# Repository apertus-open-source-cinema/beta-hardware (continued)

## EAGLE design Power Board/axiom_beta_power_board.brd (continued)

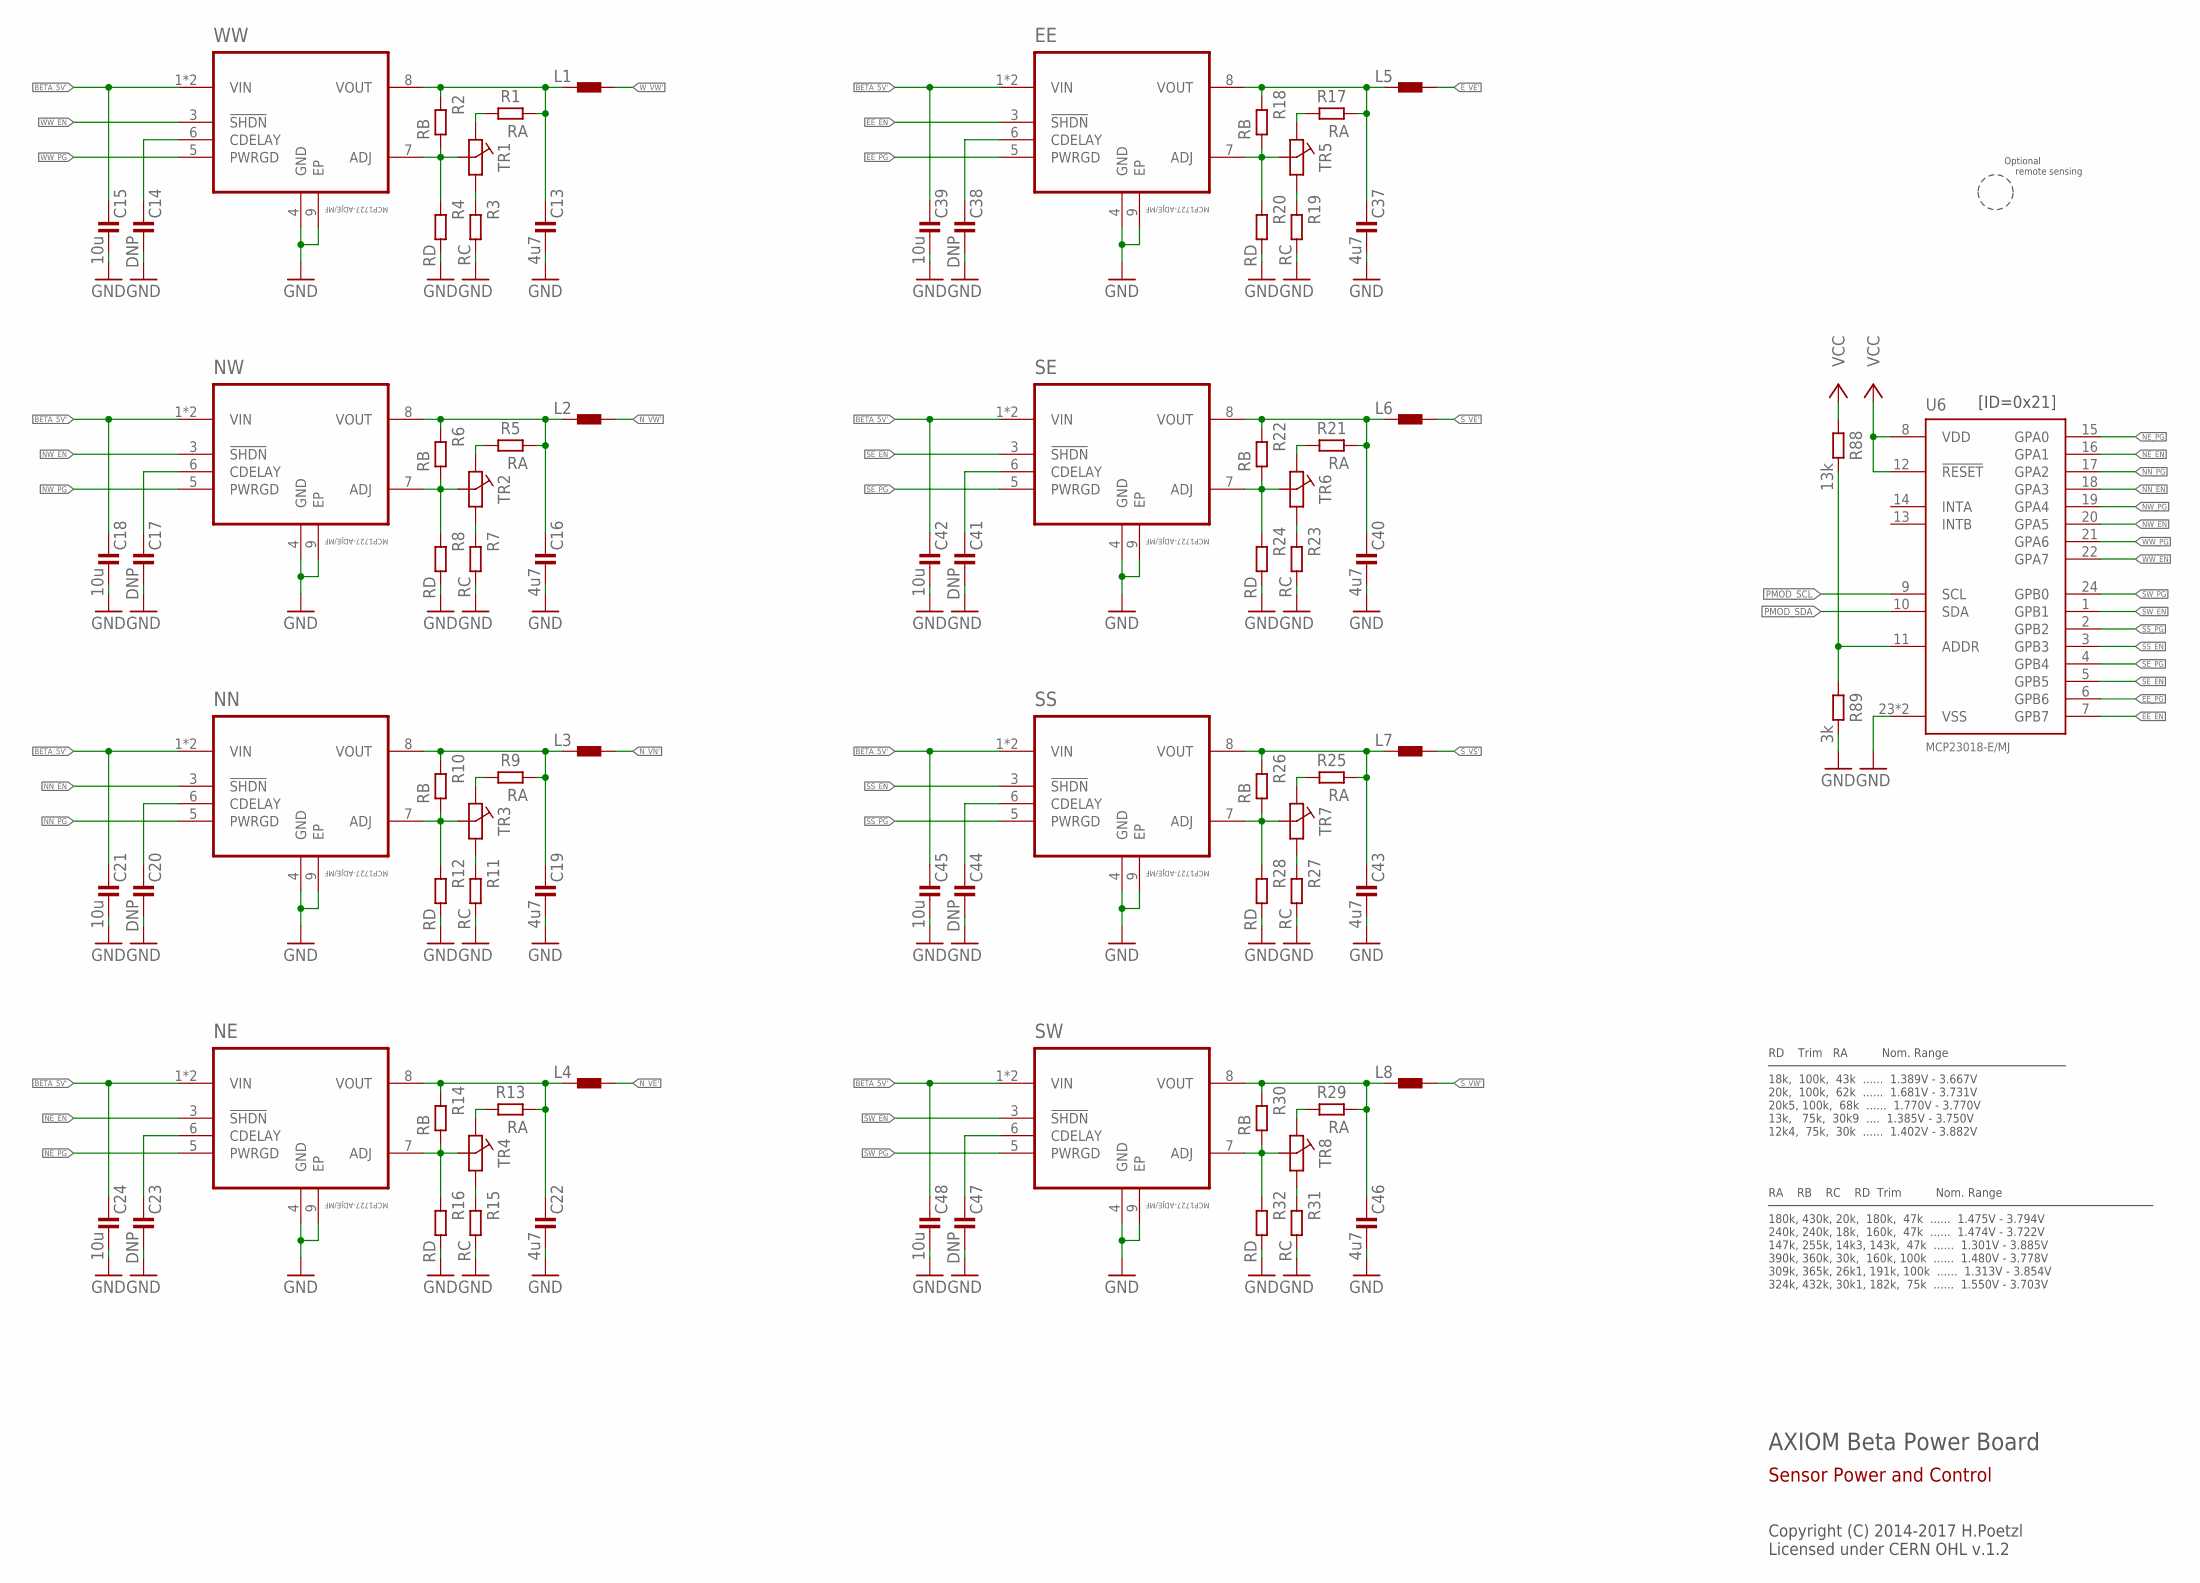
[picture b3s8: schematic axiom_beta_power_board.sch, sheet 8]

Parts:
C13, C16, C19, C22, C37, C40, C43, C46: 4u7; 0603-B
C14, C17, C20, C23, C38, C41, C44, C47: DNP; 0402-B
C15, C18, C21, C24, C39, C42, C45, C48: 10u; 0603-B
EE: MCP1727-ADJE/MF; DFN65P300X300X100-9N
L1, L2, L3, L4, L5, L6, L7, L8: L0805-B; 0805-B
NE: MCP1727-ADJE/MF; DFN65P300X300X100-9N
NN: MCP1727-ADJE/MF; DFN65P300X300X100-9N
NW: MCP1727-ADJE/MF; DFN65P300X300X100-9N
R1, R5, R9, R13, R17, R21, R25, R29: RA; 0402-B
R2, R6, R10, R14, R18, R22, R26, R30: RB; 0402-B
R3, R7, R11, R15, R19, R23, R27, R31: RC; 0402-B
R4, R8, R12, R16, R20, R24, R28, R32: RD; 0402-B
R88: 13k; 0402-B
R89: 3k; 0402-B
SE: MCP1727-ADJE/MF; DFN65P300X300X100-9N
SS: MCP1727-ADJE/MF; DFN65P300X300X100-9N
SW: MCP1727-ADJE/MF; DFN65P300X300X100-9N
TR1, TR2, TR3, TR4, TR5, TR6, TR7, TR8: PVZ2A; TRIM-PVZ2A
U6: MCP23018-E/MJ; QFN50P400X400X80-25N
WW: MCP1727-ADJE/MF; DFN65P300X300X100-9N

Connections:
BETA_5V': C15.1, C18.1, C21.1, C24.1, C39.1, C42.1, C45.1, C48.1, EE.1 (VIN), EE.2 (VIN), NE.1 (VIN), NE.2 (VIN), NN.1 (VIN), NN.2 (VIN), NW.1 (VIN), NW.2 (VIN), SE.1 (VIN), SE.2 (VIN), SS.1 (VIN), SS.2 (VIN), SW.1 (VIN), SW.2 (VIN), WW.1 (VIN), WW.2 (VIN); also elsewhere on the board
EE_EN: EE.3 (!SHDN), U6.7 (GPB7)
EE_PG: EE.5 (PWRGD), U6.6 (GPB6)
E_VE': L5.2; also elsewhere on the board
GND: C13.2, C14.2, C15.2, C16.2, C17.2, C18.2, C19.2, C20.2, C21.2, C22.2, C23.2, C24.2, C37.2, C38.2, C39.2, C40.2, C41.2, C42.2, C43.2, C44.2, C45.2, C46.2, C47.2, C48.2, EE.4 (GND), EE.9 (EP), NE.4 (GND), NE.9 (EP), NN.4 (GND), NN.9 (EP), NW.4 (GND), NW.9 (EP), R3.2, R4.2, R7.2, R8.2, R11.2, R12.2, R15.2, R16.2, R19.2, R20.2, R23.2, R24.2, R27.2, R28.2, R31.2, R32.2, R89.2, SE.4 (GND), SE.9 (EP), SS.4 (GND), SS.9 (EP), SW.4 (GND), SW.9 (EP), U6.23 (VSS), U6.25 (VSS), WW.4 (GND), WW.9 (EP); also elsewhere on the board
unnamed: C13.1, L1.1, R1.2, R2.1, WW.8 (VOUT)
unnamed: R2.2, R4.1, TR1.2 (B), WW.7 (ADJ)
unnamed: R3.1, TR1.1 (A)
unnamed: C14.1, WW.6 (CDELAY)
unnamed: R1.1, TR1.3 (C)
unnamed: C16.1, L2.1, NW.8 (VOUT), R5.2, R6.1
unnamed: NW.7 (ADJ), R6.2, R8.1, TR2.2 (B)
unnamed: R7.1, TR2.1 (A)
unnamed: C17.1, NW.6 (CDELAY)
unnamed: C19.1, L3.1, NN.8 (VOUT), R9.2, R10.1
unnamed: NN.7 (ADJ), R10.2, R12.1, TR3.2 (B)
unnamed: R5.1, TR2.3 (C)
unnamed: C20.1, NN.6 (CDELAY)
unnamed: C22.1, L4.1, NE.8 (VOUT), R13.2, R14.1
unnamed: NE.7 (ADJ), R14.2, R16.1, TR4.2 (B)
unnamed: R11.1, TR3.1 (A)
unnamed: C23.1, NE.6 (CDELAY)
unnamed: C37.1, EE.8 (VOUT), L5.1, R17.2, R18.1
unnamed: EE.7 (ADJ), R18.2, R20.1, TR5.2 (B)
unnamed: R9.1, TR3.3 (C)
unnamed: C38.1, EE.6 (CDELAY)
unnamed: R15.1, TR4.1 (A)
unnamed: C40.1, L6.1, R21.2, R22.1, SE.8 (VOUT)
unnamed: R22.2, R24.1, SE.7 (ADJ), TR6.2 (B)
unnamed: R13.1, TR4.3 (C)
unnamed: C41.1, SE.6 (CDELAY)
unnamed: R19.1, TR5.1 (A)
unnamed: C43.1, L7.1, R25.2, R26.1, SS.8 (VOUT)
unnamed: R26.2, R28.1, SS.7 (ADJ), TR7.2 (B)
unnamed: R17.1, TR5.3 (C)
unnamed: C44.1, SS.6 (CDELAY)
unnamed: R23.1, TR6.1 (A)
unnamed: C46.1, L8.1, R29.2, R30.1, SW.8 (VOUT)
unnamed: R30.2, R32.1, SW.7 (ADJ), TR8.2 (B)
unnamed: R21.1, TR6.3 (C)
unnamed: C47.1, SW.6 (CDELAY)
unnamed: R27.1, TR7.1 (A)
unnamed: R25.1, TR7.3 (C)
unnamed: R31.1, TR8.1 (A)
unnamed: R29.1, TR8.3 (C)
unnamed: R88.2, R89.1, U6.11 (ADDR)
NE_EN: NE.3 (!SHDN), U6.16 (GPA1)
NE_PG: NE.5 (PWRGD), U6.15 (GPA0)
NN_EN: NN.3 (!SHDN), U6.18 (GPA3)
NN_PG: NN.5 (PWRGD), U6.17 (GPA2)
NW_EN: NW.3 (!SHDN), U6.20 (GPA5)
NW_PG: NW.5 (PWRGD), U6.19 (GPA4)
N_VE': L4.2; also elsewhere on the board
N_VN': L3.2; also elsewhere on the board
N_VW': L2.2; also elsewhere on the board
PMOD_SCL: U6.9 (SCL); also elsewhere on the board
PMOD_SDA: U6.10 (SDA); also elsewhere on the board
SE_EN: SE.3 (!SHDN), U6.5 (GPB5)
SE_PG: SE.5 (PWRGD), U6.4 (GPB4)
SS_EN: SS.3 (!SHDN), U6.3 (GPB3)
SS_PG: SS.5 (PWRGD), U6.2 (GPB2)
SW_EN: SW.3 (!SHDN), U6.1 (GPB1)
SW_PG: SW.5 (PWRGD), U6.24 (GPB0)
S_VE': L6.2; also elsewhere on the board
S_VS': L7.2; also elsewhere on the board
S_VW': L8.2; also elsewhere on the board
VCC: R88.1, U6.8 (VDD), U6.12 (!RESET); also elsewhere on the board
WW_EN: U6.22 (GPA7), WW.3 (!SHDN)
WW_PG: U6.21 (GPA6), WW.5 (PWRGD)
W_VW': L1.2; also elsewhere on the board

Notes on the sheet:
AXIOM Beta Power Board
Copyright (C) 2014-2017 H.Poetzl Licensed under CERN OHL v.1.2
Sensor Power and Control
[ID=0x21]
RD Trim RA Nom. Range 18k, 100k, 43k ...... 1.389V - 3.667V 20k, 100k, 62k ...... 1.681V - 3.731V 20k5, 100k, 68k ...... 1.770V - 3.770V 13k, 75k, 30k9 .... 1.385V - 3.750V 12k4, 75k, 30k ...... 1.402V - 3.882V
Optional remote sensing
RA RB RC RD Trim Nom. Range 180k, 430k, 20k, 180k, 47k ...... 1.475V - 3.794V 240k, 240k, 18k, 160k, 47k ...... 1.474V - 3.722V 147k, 255k, 14k3, 143k, 47k ...... 1.301V - 3.885V 390k, 360k, 30k, 160k, 100k ...... 1.480V - 3.778V 309k, 365k, 26k1, 191k, 100k ...... 1.313V - 3.854V 324k, 432k, 30k1,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

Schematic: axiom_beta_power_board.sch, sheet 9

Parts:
R51, R52, R53, R54, R55, R56, R57, R58, R59, R60, R61, R62: R1206-B; 1206-B
R73: 750R; 0402-B
R74: 1k27; 0402-B
R75: 430R; 0402-B
R76: 0R; 0402-B
R77: 100R; 0402-B
R78: 560R; 0402-B
U17, U18, U19, U20, U23, U24: PAC1720; DFN3X3_10LEAD

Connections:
E_VE: R57.2, U19.2 (SENSE1-); also elsewhere on the board
E_VE': R57.1, U19.1 (SENSE1+); also elsewhere on the board
GND: R73.2, R74.2, R75.2, R76.2, R77.2, R78.2, U17.5 (GND), U17.EPAD (GND), U18.5 (GND), U18.EPAD (GND), U19.5 (GND), U19.EPAD (GND), U20.5 (GND), U20.EPAD (GND), U23.5 (GND), U23.EPAD (GND), U24.5 (GND), U24.EPAD (GND); also elsewhere on the board
unnamed: R73.1, U18.6 (ASEL)
unnamed: R75.1, U24.6 (ASEL)
unnamed: R78.1, U23.6 (ASEL)
unnamed: R74.1, U20.6 (ASEL)
unnamed: R76.1, U19.6 (ASEL)
unnamed: R77.1, U17.6 (ASEL)
N_VE: R54.2, U20.4 (SENSE2-); also elsewhere on the board
N_VE': R54.1, U20.3 (SENSE2+); also elsewhere on the board
N_VN: R53.2, U20.2 (SENSE1-); also elsewhere on the board
N_VN': R53.1, U20.1 (SENSE1+); also elsewhere on the board
N_VW: R52.2, U18.4 (SENSE2-); also elsewhere on the board
N_VW': R52.1, U18.3 (SENSE2+); also elsewhere on the board
PCIE_VCCIO: R61.2, U23.2 (SENSE1-)
PMOD_SCL: U17.9 (SMCLK), U18.9 (SMCLK), U19.9 (SMCLK), U20.9 (SMCLK), U23.9 (SMCLK), U24.9 (SMCLK); also elsewhere on the board
PMOD_SDA: U17.8 (SMDATA), U18.8 (SMDATA), U19.8 (SMDATA), U20.8 (SMDATA), U23.8 (SMDATA), U24.8 (SMDATA); also elsewhere on the board
S_VE: R58.2, U19.4 (SENSE2-); also elsewhere on the board
S_VE': R58.1, U19.3 (SENSE2+); also elsewhere on the board
S_VS: R59.2, U17.2 (SENSE1-); also elsewhere on the board
S_VS': R59.1, U17.1 (SENSE1+); also elsewhere on the board
S_VW: R60.2, U17.4 (SENSE2-); also elsewhere on the board
S_VW': R60.1, U17.3 (SENSE2+); also elsewhere on the board
VCC: U17.10 (VDD), U18.10 (VDD), U19.10 (VDD), U20.10 (VDD), U23.10 (VDD), U24.10 (VDD); also elsewhere on the board
VCCIO: R55.1, R56.1, R61.1, R62.1, U23.1 (SENSE1+), U23.3 (SENSE2+), U24.1 (SENSE1+), U24.3 (SENSE2+); also elsewhere on the board
VCCO_13: R56.2, U24.4 (SENSE2-); also elsewhere on the board
VCCO_34: R62.2, U23.4 (SENSE2-); also elsewhere on the board
VCCO_35: R55.2, U24.2 (SENSE1-); also elsewhere on the board
W_VW: R51.2, U18.2 (SENSE1-); also elsewhere on the board
W_VW': R51.1, U18.1 (SENSE1+); also elsewhere on the board

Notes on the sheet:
AXIOM Beta Power Board
Copyright (C) 2014-2017 H.Poetzl Licensed under CERN OHL v.1.2
Sensor Power Sensing
[0x48]
[0x49]
[0x4B]
[0x4D]
[0x4A]
[0x4C]

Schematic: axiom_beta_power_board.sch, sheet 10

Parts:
C49, C52, C55, C58, C61: 4u7; 0603-B
C50, C53, C56, C59, C62: DNP; 0402-B
C51, C54, C57, C60, C63: 10u; 0603-B
L9, L10, L11, L12, L13: L0805-A; 0805-A
MCN: MCP1727-ADJE/MF; DFN65P300X300X100-9N
MCS: MCP1727-ADJE/MF; DFN65P300X300X100-9N
MXN: MCP1727-ADJE/MF; DFN65P300X300X100-9N
MXS: MCP1727-ADJE/MF; DFN65P300X300X100-9N
R33, R35, R39, R41: RD; 0402-B
R34, R36, R40, R42: RC; 0402-B
R37: 102k; 0402-B
R38: 20k; 0402-B
R67, R68, R69, R70, R71, R72: R1206-B; 1206-B
R81: 2k0; 0402-B
R82: 1k6; 0402-B
R83: 2k7; 0402-B
R90: 15k; 0402-B
R91: 1k; 0402-B
U7: MCP23018-E/MJ; QFN50P400X400X80-25N
U14, U15, U22: PAC1720; DFN3X3_10LEAD
VIO: MCP1727-ADJE/MF; DFN65P300X300X100-9N

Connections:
BETA_5V: R70.1, U22.3 (SENSE2+); also elsewhere on the board
BETA_5V': C51.1, C54.1, C57.1, C60.1, C63.1, MCN.1 (VIN), MCN.2 (VIN), MCS.1 (VIN), MCS.2 (VIN), MXN.1 (VIN), MXN.2 (VIN), MXS.1 (VIN), MXS.2 (VIN), R70.2, U22.4 (SENSE2-), VIO.1 (VIN), VIO.2 (VIN); also elsewhere on the board
CSO_NE_V: R67.2, U14.2 (SENSE1-); also elsewhere on the board
CSO_N_V': L12.2, R67.1, U14.1 (SENSE1+)
CSO_SW_V: R71.2, U15.2 (SENSE1-); also elsewhere on the board
CSO_S_V': L10.2, R71.1, U15.1 (SENSE1+)
GND: C49.2, C50.2, C51.2, C52.2, C53.2, C54.2, C55.2, C56.2, C57.2, C58.2, C59.2, C60.2, C61.2, C62.2, C63.2, MCN.4 (GND), MCN.9 (EP), MCS.4 (GND), MCS.9 (EP), MXN.4 (GND), MXN.9 (EP), MXS.4 (GND), MXS.9 (EP), R34.2, R36.2, R38.2, R40.2, R42.2, R81.2, R82.2, R83.2, R91.2, U7.23 (VSS), U7.25 (VSS), U14.5 (GND), U14.EPAD (GND), U15.5 (GND), U15.EPAD (GND), U22.5 (GND), U22.EPAD (GND), VIO.4 (GND), VIO.9 (EP); also elsewhere on the board
MCN_EN: MCN.3 (!SHDN), U7.18 (GPA3)
MCN_PG: MCN.5 (PWRGD), U7.17 (GPA2)
MCS_EN: MCS.3 (!SHDN), U7.22 (GPA7)
MCS_PG: MCS.5 (PWRGD), U7.21 (GPA6)
MXN_EN: MXN.3 (!SHDN), U7.16 (GPA1)
MXN_PG: MXN.5 (PWRGD), U7.15 (GPA0)
MXS_EN: MXS.3 (!SHDN), U7.1 (GPB1)
MXS_PG: MXS.5 (PWRGD), U7.24 (GPB0)
unnamed: C49.1, L9.1, MXS.8 (VOUT), R41.1
unnamed: MXS.7 (ADJ), R41.2, R42.1
unnamed: C50.1, MXS.6 (CDELAY)
unnamed: R81.1, U14.6 (ASEL)
unnamed: R83.1, U15.6 (ASEL)
unnamed: C52.1, L10.1, MCS.8 (VOUT), R39.1
unnamed: MCS.7 (ADJ), R39.2, R40.1
unnamed: C53.1, MCS.6 (CDELAY)
unnamed: R82.1, U22.6 (ASEL)
unnamed: C55.1, L11.1, R37.1, VIO.8 (VOUT)
unnamed: R37.2, R38.1, VIO.7 (ADJ)
unnamed: C56.1, VIO.6 (CDELAY)
unnamed: C58.1, L12.1, MCN.8 (VOUT), R35.1
unnamed: MCN.7 (ADJ), R35.2, R36.1
unnamed: C59.1, MCN.6 (CDELAY)
unnamed: C61.1, L13.1, MXN.8 (VOUT), R33.1
unnamed: MXN.7 (ADJ), R33.2, R34.1
unnamed: C62.1, MXN.6 (CDELAY)
unnamed: R90.2, R91.1, U7.11 (ADDR)
PCIE_N_V: R68.2, U14.4 (SENSE2-); also elsewhere on the board
PCIE_N_V': L13.2, R68.1, U14.3 (SENSE2+)
PCIE_S_V: R72.2, U15.4 (SENSE2-); also elsewhere on the board
PCIE_S_V': L9.2, R72.1, U15.3 (SENSE2+)
PMOD_SCL: U7.9 (SCL), U14.9 (SMCLK), U15.9 (SMCLK), U22.9 (SMCLK); also elsewhere on the board
PMOD_SDA: U7.10 (SDA), U14.8 (SMDATA), U15.8 (SMDATA), U22.8 (SMDATA); also elsewhere on the board
VCC: R90.1, U7.8 (VDD), U7.12 (!RESET), U14.10 (VDD), U15.10 (VDD), U22.10 (VDD); also elsewhere on the board
VCCIO: L11.2; also elsewhere on the board
VIO_EN: U7.20 (GPA5), VIO.3 (!SHDN)
VIO_PG: U7.19 (GPA4), VIO.5 (PWRGD)
ZED_5V: R69.1, U22.1 (SENSE1+); also elsewhere on the board
ZED_5V': R69.2, U22.2 (SENSE1-); also elsewhere on the board

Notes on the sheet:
AXIOM Beta Power Board
Copyright (C) 2014-2017 H.Poetzl Licensed under CERN OHL v.1.2
Power, Control and Sensing
[ID=0x20]
[0x29]
[0x28]
[0x2A]

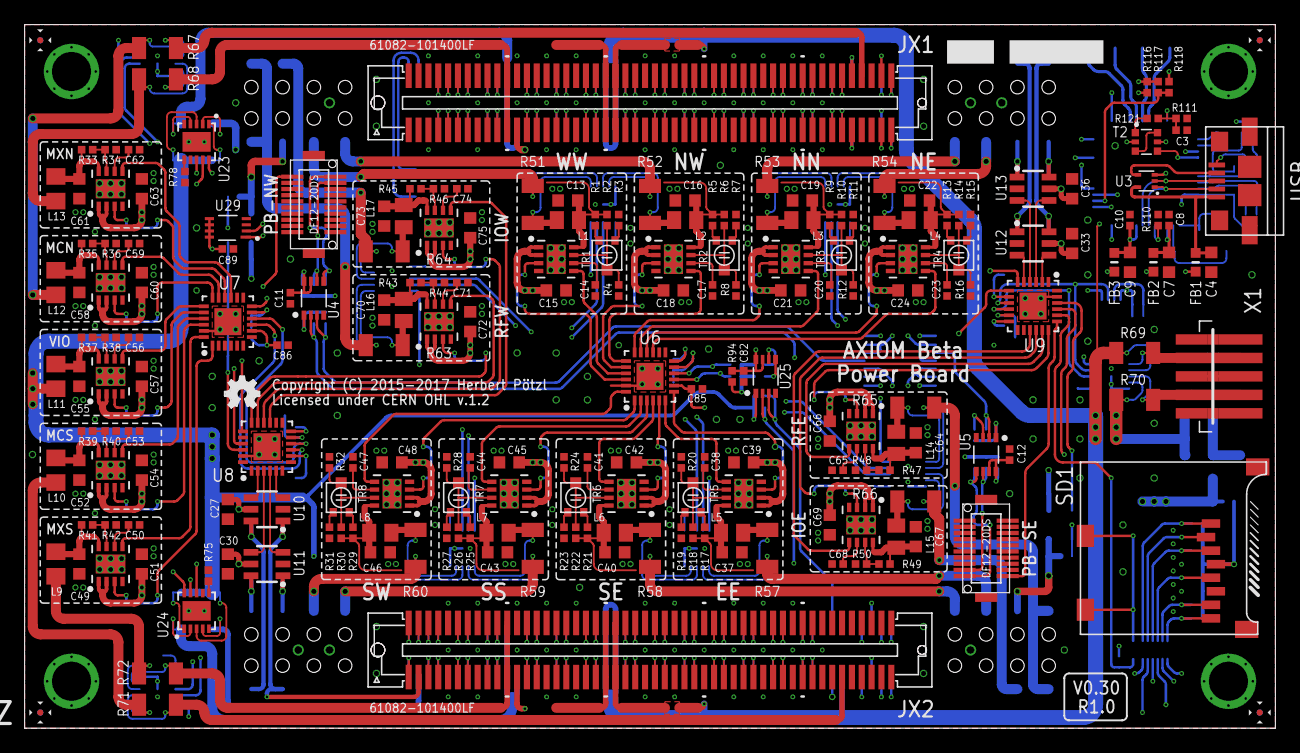
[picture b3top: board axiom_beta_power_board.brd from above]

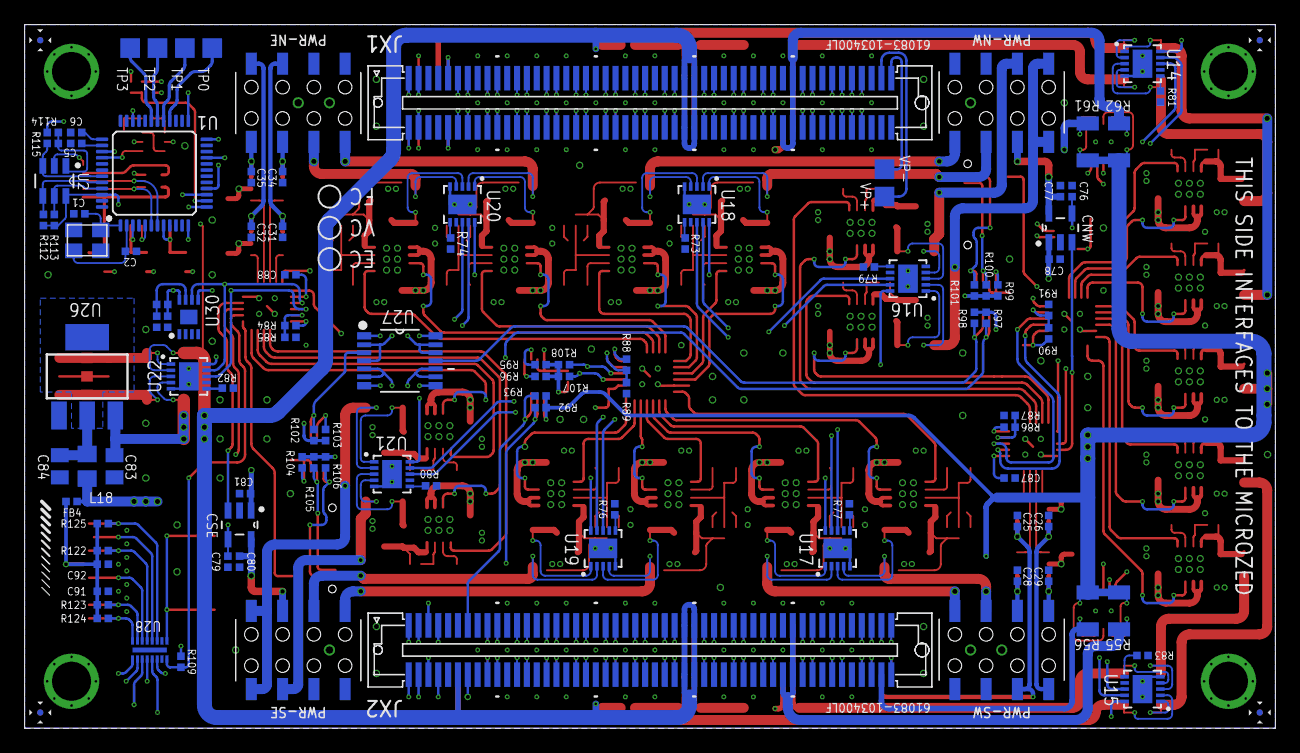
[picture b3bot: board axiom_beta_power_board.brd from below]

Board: 4 copper layers, 101.6 x 57.1 mm, 316 parts (104 on the bottom side), 370 nets.

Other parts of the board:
LOGO1: OSHW_LOGO_FILLX0100-NT; OSHW_FILLX100_NOTEXT

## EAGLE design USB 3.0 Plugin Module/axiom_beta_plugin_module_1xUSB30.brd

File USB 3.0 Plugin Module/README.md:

# AXIOM Beta 1x USB 3.0 Plugin Module v0.2 R1.1

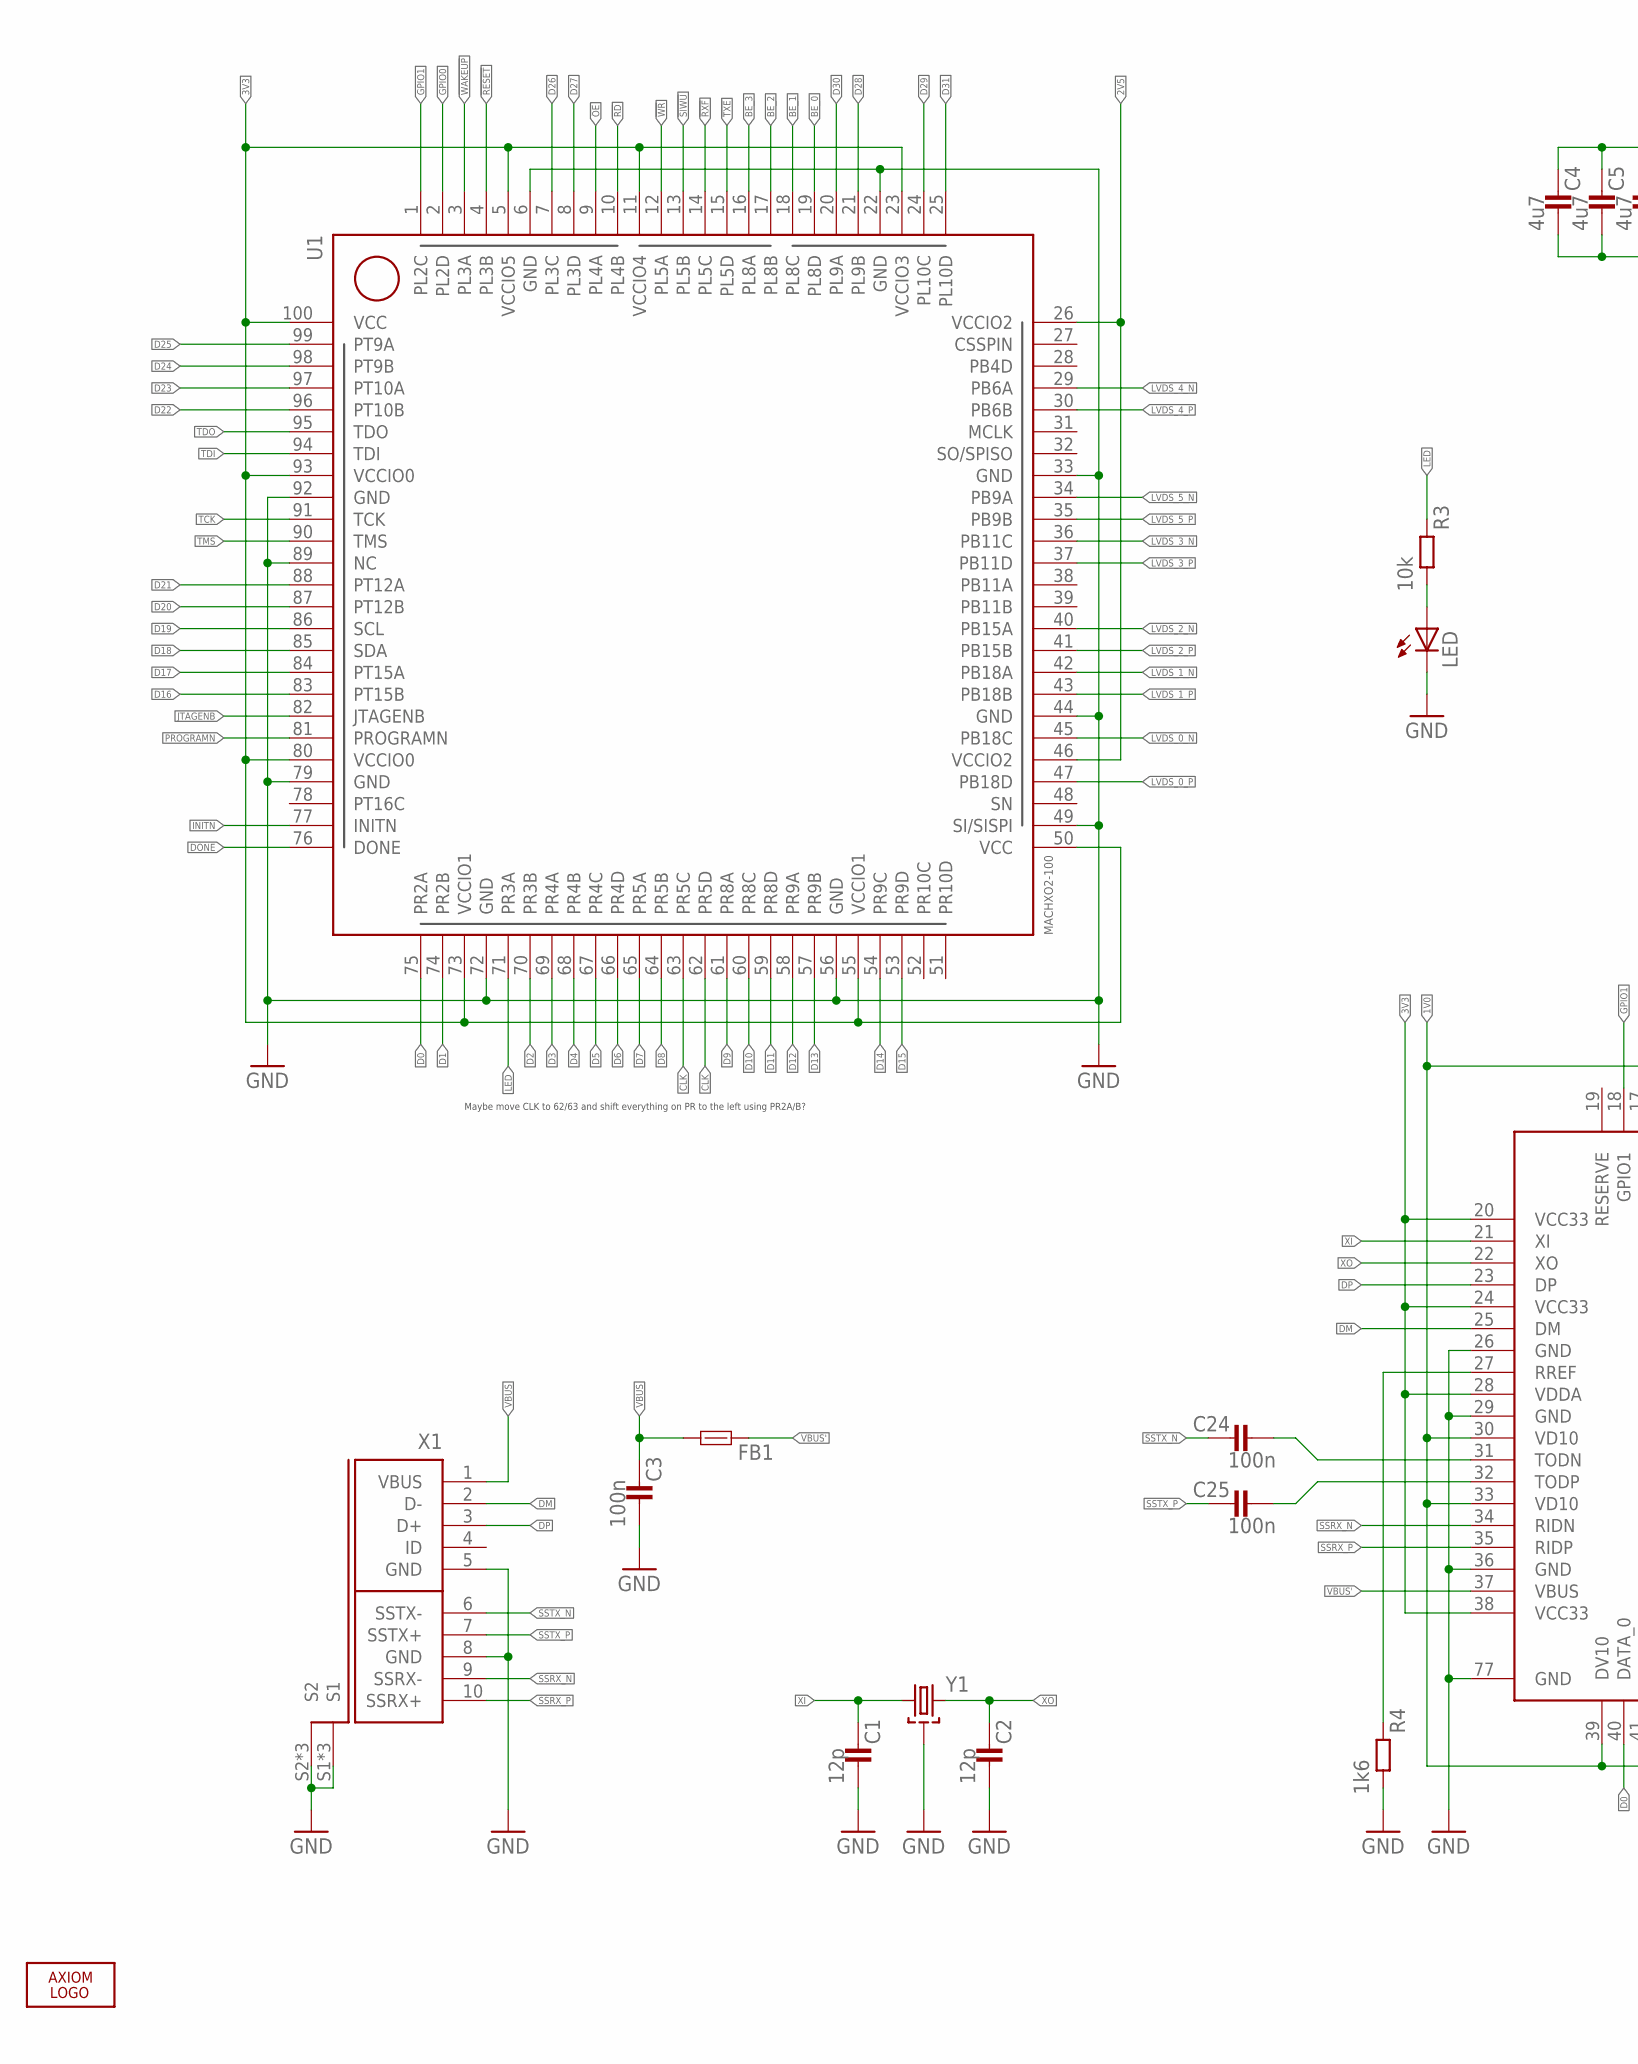
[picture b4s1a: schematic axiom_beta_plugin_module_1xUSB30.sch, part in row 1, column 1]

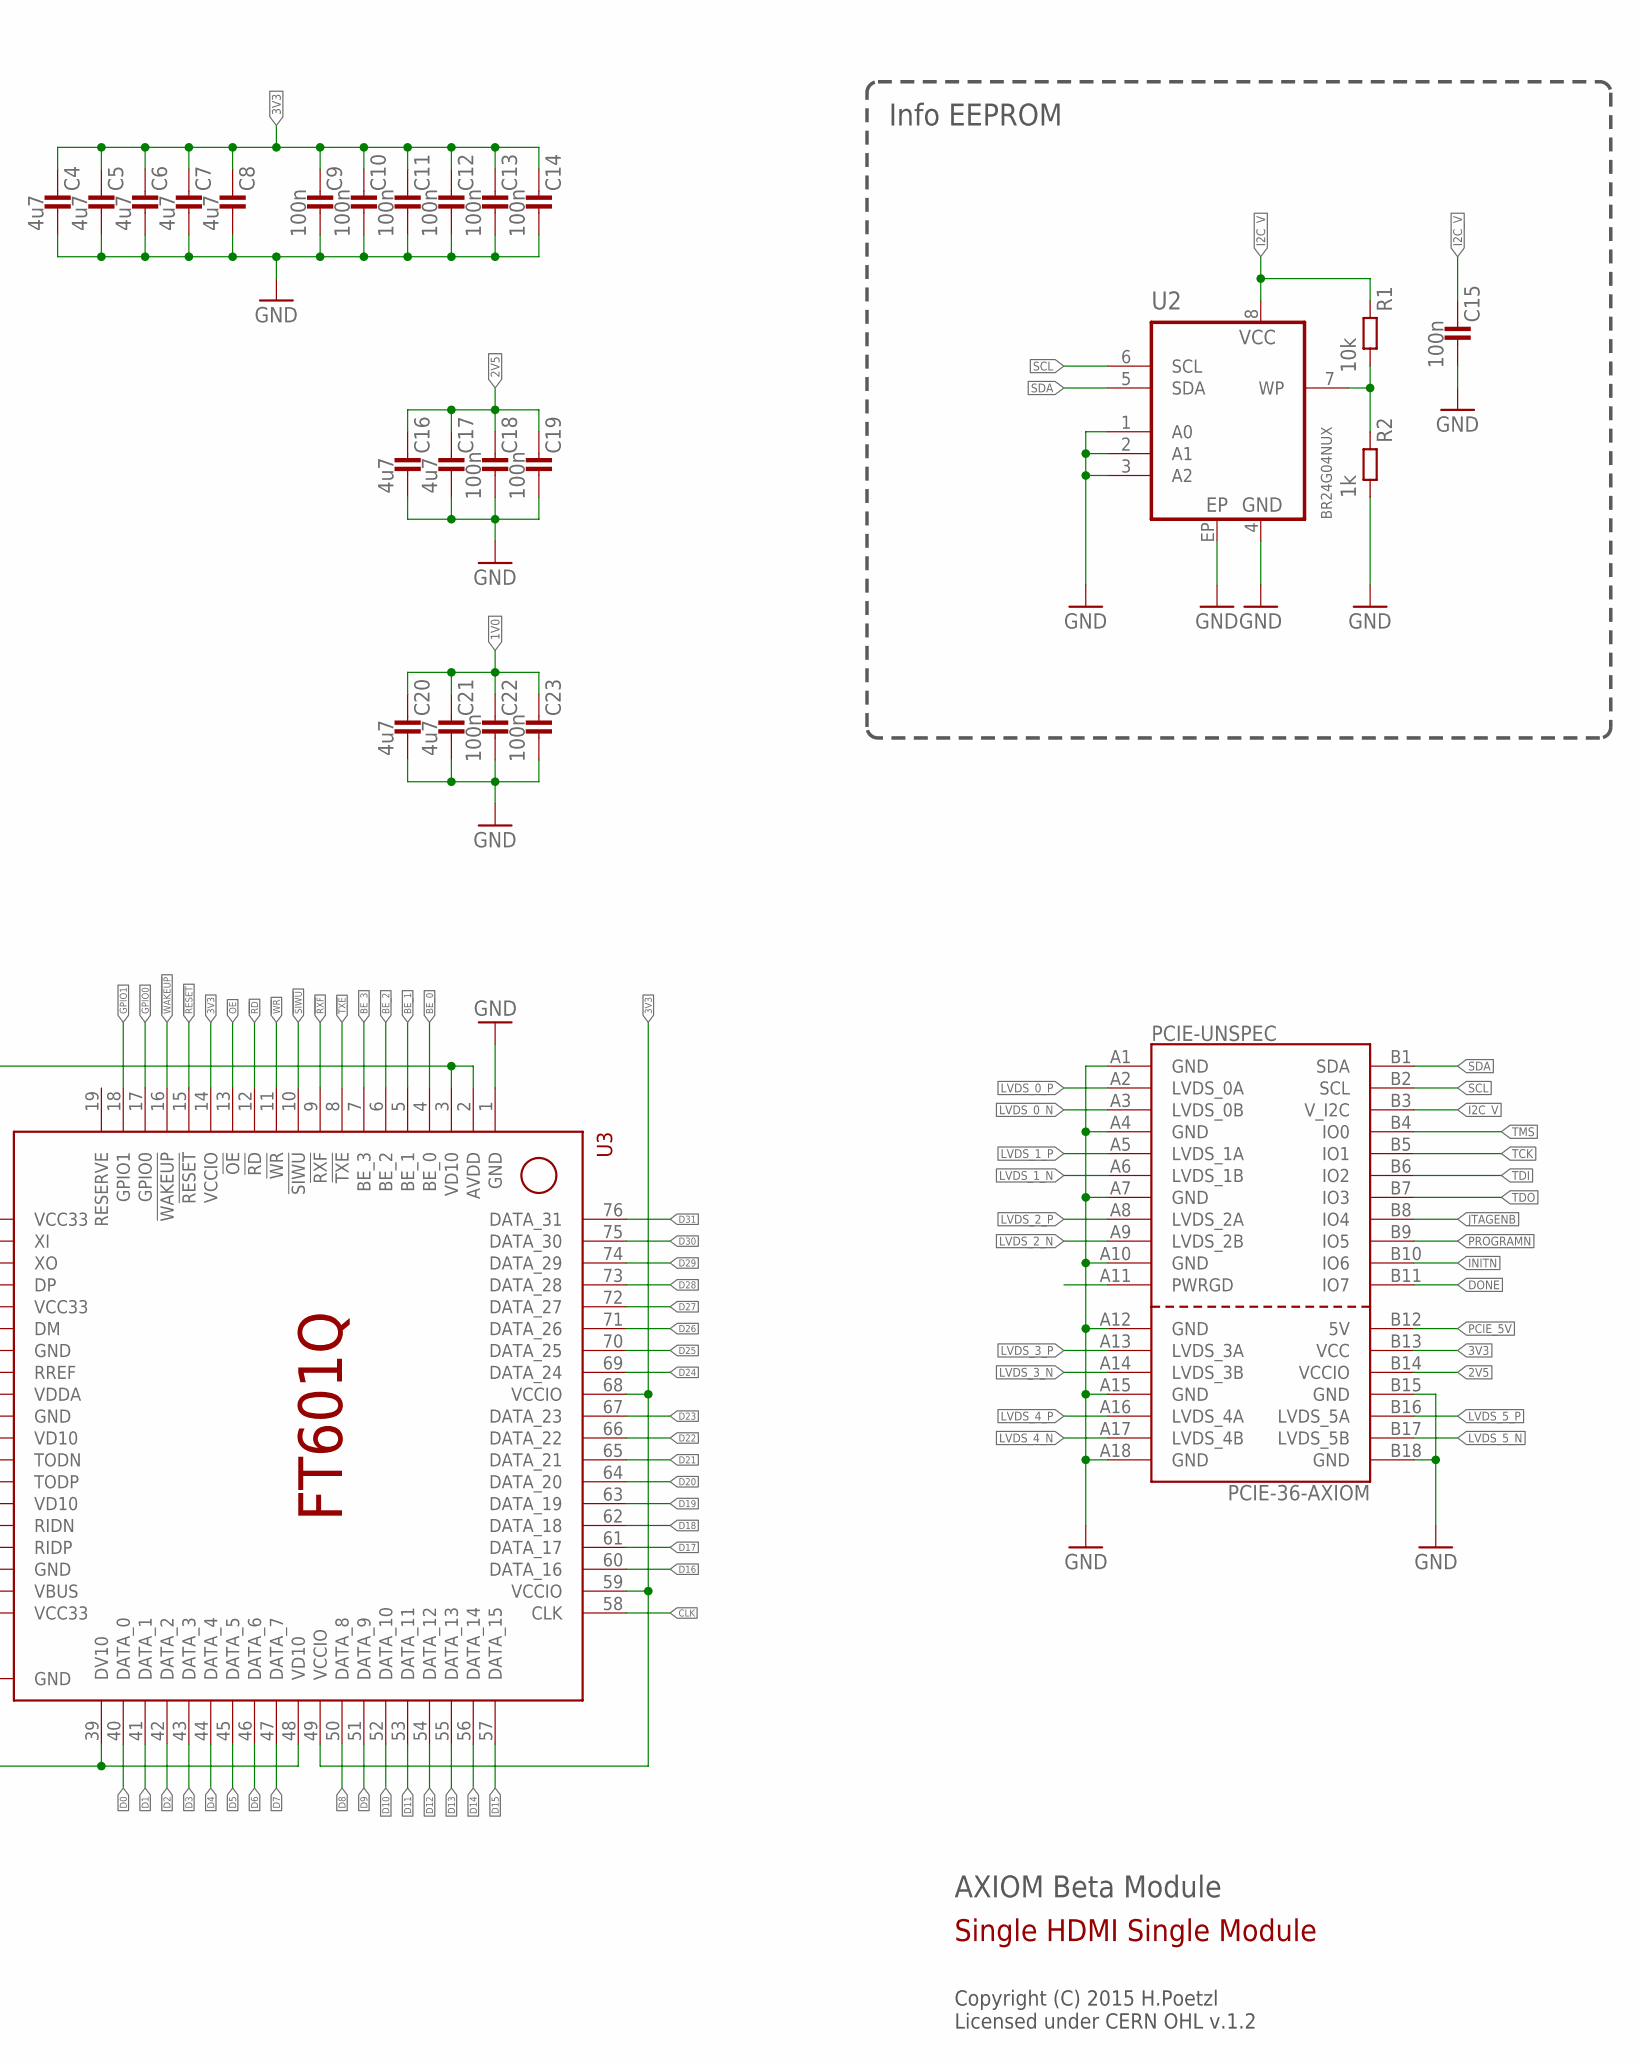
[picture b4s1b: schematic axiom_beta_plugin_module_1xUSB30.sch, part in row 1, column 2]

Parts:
C1, C2: 12p; 0402-C
C3, C9, C10, C11, C12, C13, C14, C15, C18, C19, C22, C23: 100n; 0402-C
C4, C5, C6, C7, C8, C16, C17, C20, C21: 4u7; 0402-C
C24, C25: 100n; 0201-C
FB1: FB0402-C; 0402-C
LED: LED; CHIPLED_0603
PCIE-UNSPEC: PCIE-36-AXIOM
R1: 10k; 0402-C
R2: 1k; 0402-C
R3: 10k; 0402-B
R4: 1k6; 0201-C
U1: MACHXO2-100; MACHXO2-100TQFP
U2: BR24G04NUX; DFN200X300X100-9N
U3: FT601QQFN76; QFN76
U$: AXIOM_LOGO328X50; AXIOM_LOGO_328X50
X1: 10_USB_3.0_2S-SMT; MICRO-B-30-H-SMT
Y1: SMD-4P-2G-2.0X1.6; 2.0X1.6

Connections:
1V0: C20.1, C21.1, C22.1, C23.1, U3.2 (AVDD), U3.3 (VD10), U3.30 (VD10), U3.33 (VD10), U3.39 (DV10), U3.48 (VD10)
2V5: C16.1, C17.1, C18.1, C19.1, PCIE-UNSPEC.B14 (VCCIO), U1.26 (VCCIO2), U1.46 (VCCIO2)
3V3: C4.1, C5.1, C6.1, C7.1, C8.1, C9.1, C10.1, C11.1, C12.1, C13.1, C14.1, PCIE-UNSPEC.B13 (VCC), U1.5 (VCCIO5), U1.11 (VCCIO4), U1.23 (VCCIO3), U1.50 (VCC), U1.55 (VCCIO1), U1.73 (VCCIO1), U1.80 (VCCIO0), U1.93 (VCCIO0), U1.100 (VCC), U3.14 (VCCIO), U3.20 (VCC33), U3.24 (VCC33), U3.28 (VDDA), U3.38 (VCC33), U3.49 (VCCIO), U3.59 (VCCIO), U3.68 (VCCIO)
!OE: U1.9 (PL4A), U3.13 (!OE)
!RD: U1.10 (PL4B), U3.12 (!RD)
!RESET: U1.4 (PL3B), U3.15 (!RESET)
!RXF: U1.14 (PL5C), U3.9 (!RXF)
!SIWU: U1.13 (PL5B), U3.10 (!SIWU)
!TXE: U1.15 (PL5D), U3.8 (!TXE)
!WAKEUP: U1.3 (PL3A), U3.16 (!WAKEUP)
!WR: U1.12 (PL5A), U3.11 (!WR)
BE_0: U1.19 (PL8D), U3.4 (BE_0)
BE_1: U1.18 (PL8C), U3.5 (BE_1)
BE_2: U1.17 (PL8B), U3.6 (BE_2)
BE_3: U1.16 (PL8A), U3.7 (BE_3)
CLK: U1.62 (PR5D), U1.63 (PR5C), U3.58 (CLK)
D0: U1.75 (PR2A), U3.40 (DATA_0)
D1: U1.74 (PR2B), U3.41 (DATA_1)
D2: U1.70 (PR3B), U3.42 (DATA_2)
D3: U1.69 (PR4A), U3.43 (DATA_3)
D4: U1.68 (PR4B), U3.44 (DATA_4)
D5: U1.67 (PR4C), U3.45 (DATA_5)
D6: U1.66 (PR4D), U3.46 (DATA_6)
D7: U1.65 (PR5A), U3.47 (DATA_7)
D8: U1.64 (PR5B), U3.50 (DATA_8)
D9: U1.61 (PR8A), U3.51 (DATA_9)
D10: U1.60 (PR8C), U3.52 (DATA_10)
D11: U1.59 (PR8D), U3.53 (DATA_11)
D12: U1.58 (PR9A), U3.54 (DATA_12)
D13: U1.57 (PR9B), U3.55 (DATA_13)
D14: U1.54 (PR9C), U3.56 (DATA_14)
D15: U1.53 (PR9D), U3.57 (DATA_15)
D16: U1.83 (PT15B), U3.60 (DATA_16)
D17: U1.84 (PT15A), U3.61 (DATA_17)
D18: U1.85 (SDA), U3.62 (DATA_18)
D19: U1.86 (SCL), U3.63 (DATA_19)
D20: U1.87 (PT12B), U3.64 (DATA_20)
D21: U1.88 (PT12A), U3.65 (DATA_21)
D22: U1.96 (PT10B), U3.66 (DATA_22)
D23: U1.97 (PT10A), U3.67 (DATA_23)
D24: U1.98 (PT9B), U3.69 (DATA_24)
D25: U1.99 (PT9A), U3.70 (DATA_25)
D26: U1.7 (PL3C), U3.71 (DATA_26)
D27: U1.8 (PL3D), U3.72 (DATA_27)
D28: U1.21 (PL9B), U3.73 (DATA_28)
D29: U1.24 (PL10C), U3.74 (DATA_29)
D30: U1.20 (PL9A), U3.75 (DATA_30)
D31: U1.25 (PL10D), U3.76 (DATA_31)
DM: U3.25 (DM), X1.2 (D-)
DONE: PCIE-UNSPEC.B11 (IO7), U1.76 (DONE)
DP: U3.23 (DP), X1.3 (D+)
GND: C1.2, C2.2, C3.2, C4.2, C5.2, C6.2, C7.2, C8.2, C9.2, C10.2, C11.2, C12.2, C13.2, C14.2, C15.2, C16.2, C17.2, C18.2, C19.2, C20.2, C21.2, C22.2, C23.2, LED.C, PCIE-UNSPEC.A1 (GND), PCIE-UNSPEC.A4 (GND), PCIE-UNSPEC.A7 (GND), PCIE-UNSPEC.A10 (GND), PCIE-UNSPEC.A12 (GND), PCIE-UNSPEC.A15 (GND), PCIE-UNSPEC.A18 (GND), PCIE-UNSPEC.B15 (GND), PCIE-UNSPEC.B18 (GND), R2.2, R4.2, U1.6 (GND), U1.22 (GND), U1.33 (GND), U1.44 (GND), U1.49 (SI/SISPI), U1.56 (GND), U1.72 (GND), U1.79 (GND), U1.89 (NC), U1.92 (GND), U2.1 (A0), U2.2 (A1), U2.3 (A2), U2.4 (GND), U2.EP, U3.1 (GND), U3.26 (GND), U3.29 (GND), U3.36 (GND), U3.77 (GND), X1.5 (GND), X1.8 (GND), X1.S1, X1.S2, X1.Z1 (S1), X1.Z2 (S1), X1.Z3 (S2), X1.Z4 (S2), Y1.2 (GND), Y1.4 (GND)
GPIO0: U1.2 (PL2D), U3.17 (GPIO0)
GPIO1: U1.1 (PL2C), U3.18 (GPIO1)
I2C_V: C15.1, PCIE-UNSPEC.B3 (V_I2C), R1.1, U2.8 (VCC)
INITN: PCIE-UNSPEC.B10 (IO6), U1.77 (INITN)
JTAGENB: PCIE-UNSPEC.B8 (IO4), U1.82 (JTAGENB)
LED: R3.1, U1.71 (PR3A)
LVDS_0_N: PCIE-UNSPEC.A3 (LVDS_0B), U1.45 (PB18C)
LVDS_0_P: PCIE-UNSPEC.A2 (LVDS_0A), U1.47 (PB18D)
LVDS_1_N: PCIE-UNSPEC.A6 (LVDS_1B), U1.42 (PB18A)
LVDS_1_P: PCIE-UNSPEC.A5 (LVDS_1A), U1.43 (PB18B)
LVDS_2_N: PCIE-UNSPEC.A9 (LVDS_2B), U1.40 (PB15A)
LVDS_2_P: PCIE-UNSPEC.A8 (LVDS_2A), U1.41 (PB15B)
LVDS_3_N: PCIE-UNSPEC.A14 (LVDS_3B), U1.36 (PB11C)
LVDS_3_P: PCIE-UNSPEC.A13 (LVDS_3A), U1.37 (PB11D)
LVDS_4_N: PCIE-UNSPEC.A17 (LVDS_4B), U1.29 (PB6A)
LVDS_4_P: PCIE-UNSPEC.A16 (LVDS_4A), U1.30 (PB6B)
LVDS_5_N: PCIE-UNSPEC.B17 (LVDS_5B), U1.34 (PB9A)
LVDS_5_P: PCIE-UNSPEC.B16 (LVDS_5A), U1.35 (PB9B)
unnamed: LED.A, R3.2
unnamed: R4.1, U3.27 (RREF)
unnamed: R1.2, R2.1, U2.7 (WP)
PCIE_5V: PCIE-UNSPEC.B12 (5V)
PROGRAMN: PCIE-UNSPEC.B9 (IO5), U1.81 (PROGRAMN)
SCL: PCIE-UNSPEC.B2 (SCL), U2.6 (SCL)
SDA: PCIE-UNSPEC.B1 (SDA), U2.5 (SDA)
SSRX_N: U3.34 (RIDN), X1.9 (SSRX-)
SSRX_P: U3.35 (RIDP), X1.10 (SSRX+)
SSTX_N: C24.1, X1.6 (SSTX-)
SSTX_P: C25.1, X1.7 (SSTX+)
TCK: PCIE-UNSPEC.B5 (IO1), U1.91 (TCK)
TDI: PCIE-UNSPEC.B6 (IO2), U1.94 (TDI)
TDO: PCIE-UNSPEC.B7 (IO3), U1.95 (TDO)
TMS: PCIE-UNSPEC.B4 (IO0), U1.90 (TMS)
TOD_N: C24.2, U3.31 (TODN)
TOD_P: C25.2, U3.32 (TODP)
VBUS: C3.1, FB1.2, X1.1 (VBUS)
VBUS': FB1.1, U3.37 (VBUS)
XI: C1.1, U3.21 (XI), Y1.1
XO: C2.1, U3.22 (XO), Y1.3 (2)

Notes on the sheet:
AXIOM Beta Module
Copyright (C) 2015 H.Poetzl Licensed under CERN OHL v.1.2
Single HDMI Single Module
Info EEPROM
Maybe move CLK to 62/63 and shift everything on PR to the left using PR2A/B?

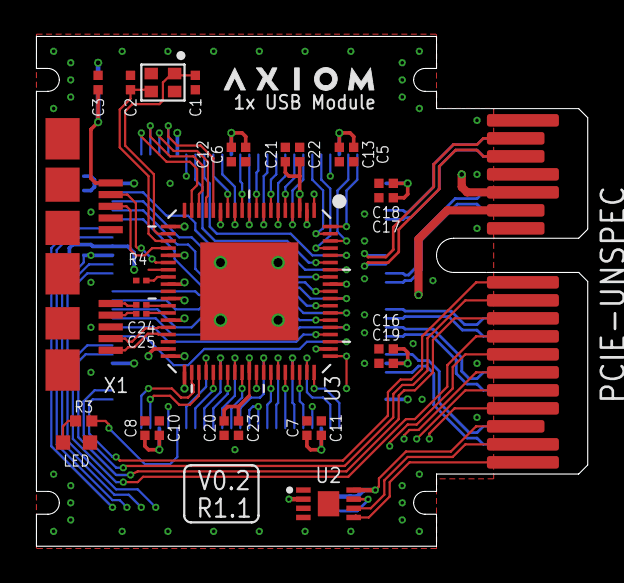
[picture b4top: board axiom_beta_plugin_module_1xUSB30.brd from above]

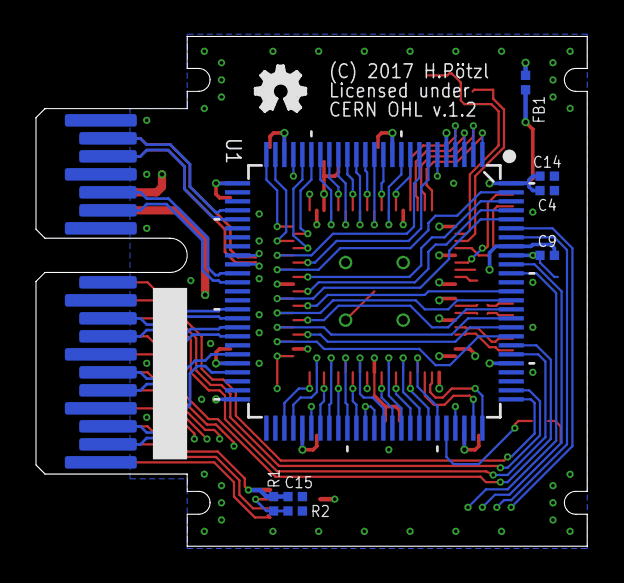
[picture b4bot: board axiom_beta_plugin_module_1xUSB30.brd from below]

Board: 4 copper layers, 30.6 x 28.3 mm, 39 parts (9 on the bottom side), 90 nets.

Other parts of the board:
LOGO2: OSHW_LOGO_FILLX0100-NT; OSHW_FILLX100_NOTEXT
